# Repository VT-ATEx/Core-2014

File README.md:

Core-2014
=========

Core systems for the 2014 - 2015 school year

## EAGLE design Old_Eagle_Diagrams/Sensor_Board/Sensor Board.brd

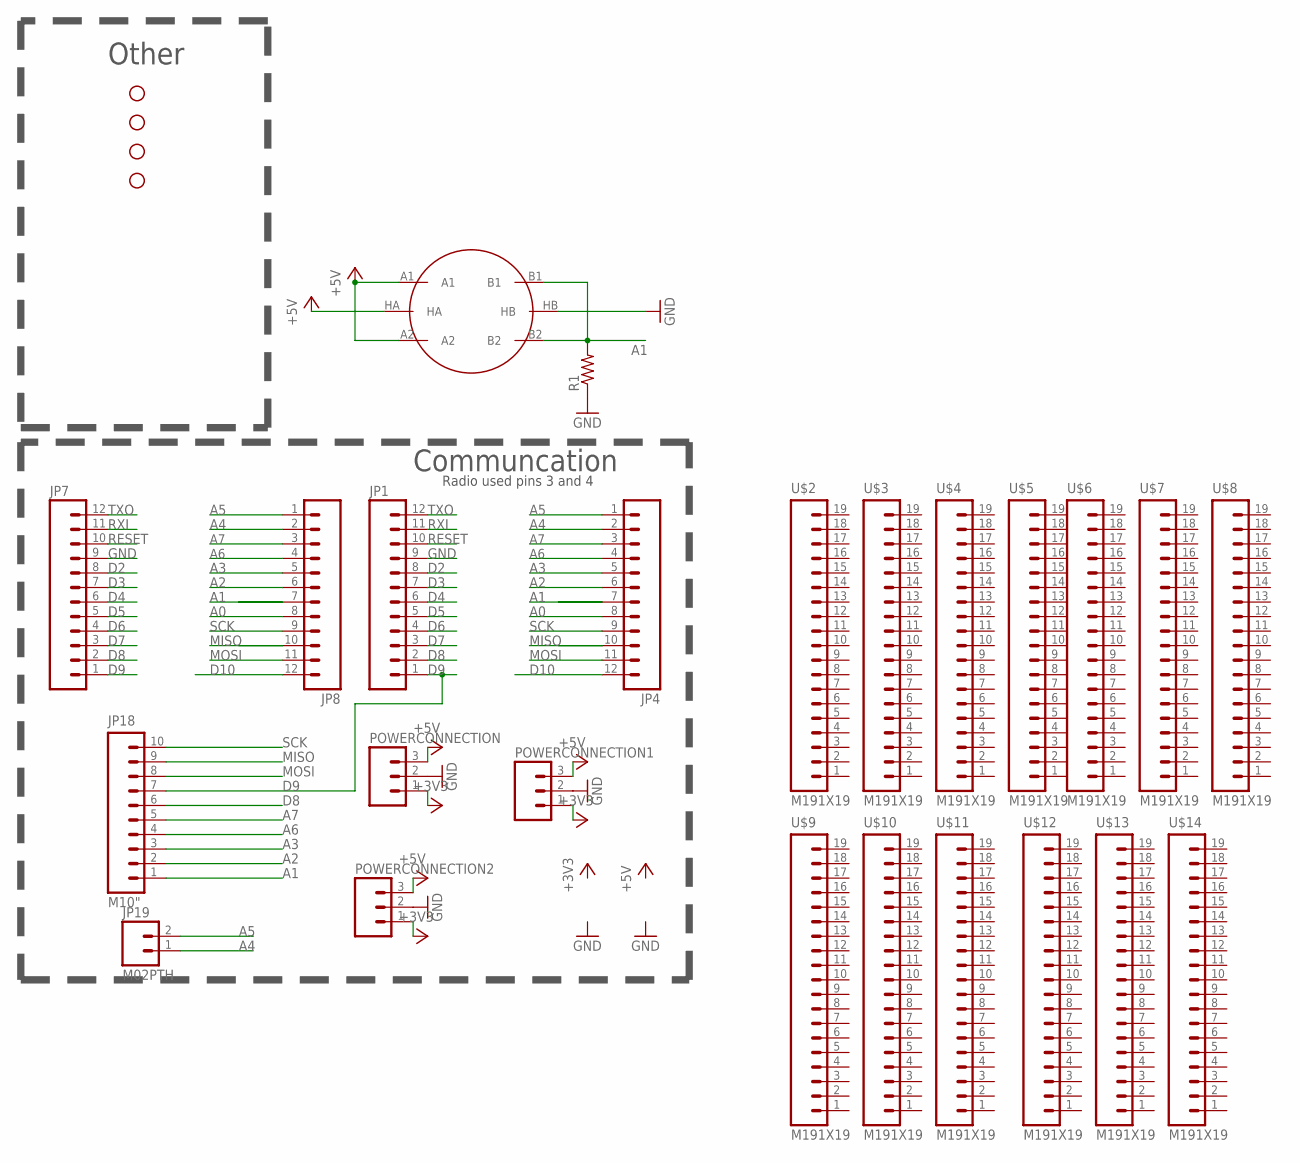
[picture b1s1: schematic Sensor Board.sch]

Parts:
JP1, JP4, JP7, JP8: M12PTH; 1X12
JP18: M10"; 1X10
JP19: M02PTH; 1X02
POWERCONNECTION, POWERCONNECTION1, POWERCONNECTION2: M03PTH; 1X03
R1: RESISTORPTH-1/4W; AXIAL-0.4
STANDOFF1, STANDOFF2, STANDOFF3, STANDOFF4: STAND-OFF
U$1: GAS_SOCKET; MQ-3
U$2, U$3, U$4, U$5, U$6, U$7, U$8, U$9, U$10, U$11, U$12, U$13, U$14: M191X19; 1X19

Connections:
+3V3: POWERCONNECTION.1, POWERCONNECTION1.1, POWERCONNECTION2.1
+5V: POWERCONNECTION.3, POWERCONNECTION1.3, POWERCONNECTION2.3, U$1.A1, U$1.A2, U$1.HA
A0: JP4.8, JP8.8
A1: JP4.7, JP8.7, JP18.1, R1.P$2 (2), U$1.B1, U$1.B2
A2: JP4.6, JP8.6, JP18.2
A3: JP4.5, JP8.5, JP18.3
A4: JP4.2, JP8.2, JP19.1
A5: JP4.1, JP8.1, JP19.2
A6: JP4.4, JP8.4, JP18.4
A7: JP4.3, JP8.3, JP18.5
D2: JP1.8, JP7.8
D3: JP1.7, JP7.7
D4: JP1.6, JP7.6
D5: JP1.5, JP7.5
D6: JP1.4, JP7.4
D7: JP1.3, JP7.3
D8: JP1.2, JP7.2, JP18.6
D9: JP1.1, JP7.1, JP18.7
D10: JP4.12, JP8.12
GND: JP1.9, JP7.9, POWERCONNECTION.2, POWERCONNECTION1.2, POWERCONNECTION2.2, R1.P$1 (1), U$1.HB
MISO: JP4.10, JP8.10, JP18.9
MOSI: JP4.11, JP8.11, JP18.8
RESET: JP1.10, JP7.10
RXI: JP1.11, JP7.11
SCK: JP4.9, JP8.9, JP18.10
TXO: JP1.12, JP7.12

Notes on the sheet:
Communcation
Other
Radio used pins 3 and 4

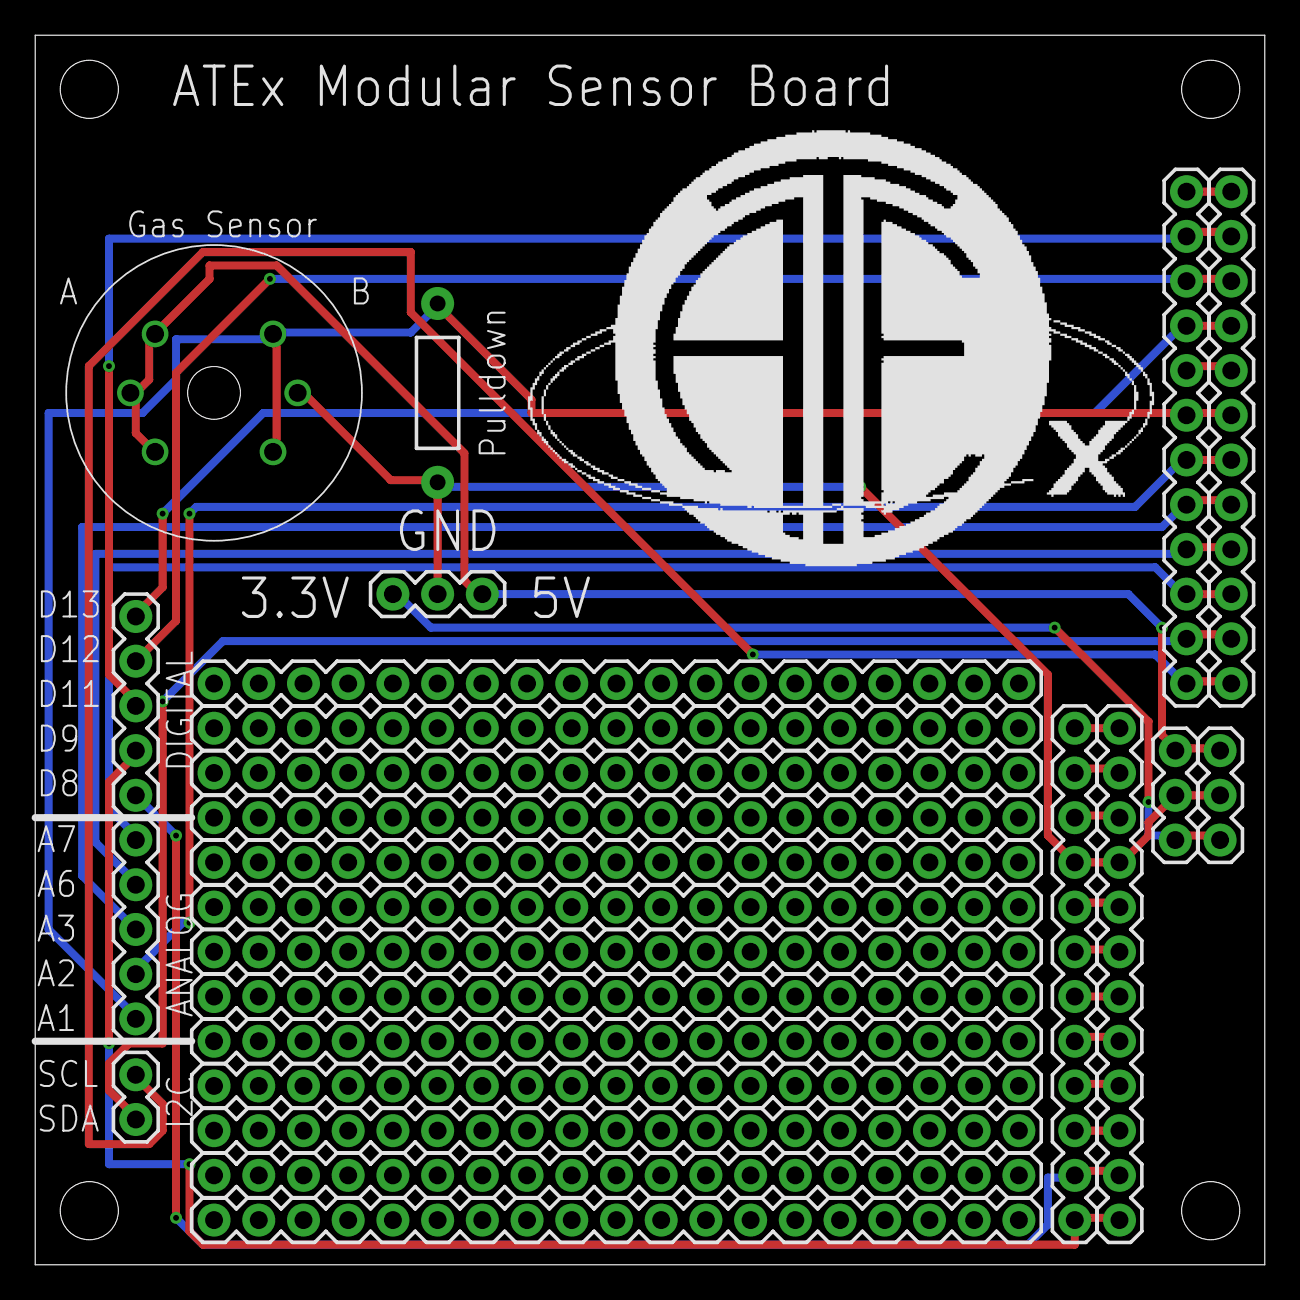
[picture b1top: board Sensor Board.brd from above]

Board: 2 copper layers, 69.8 x 69.8 mm, 28 parts (0 on the bottom side), 26 nets.

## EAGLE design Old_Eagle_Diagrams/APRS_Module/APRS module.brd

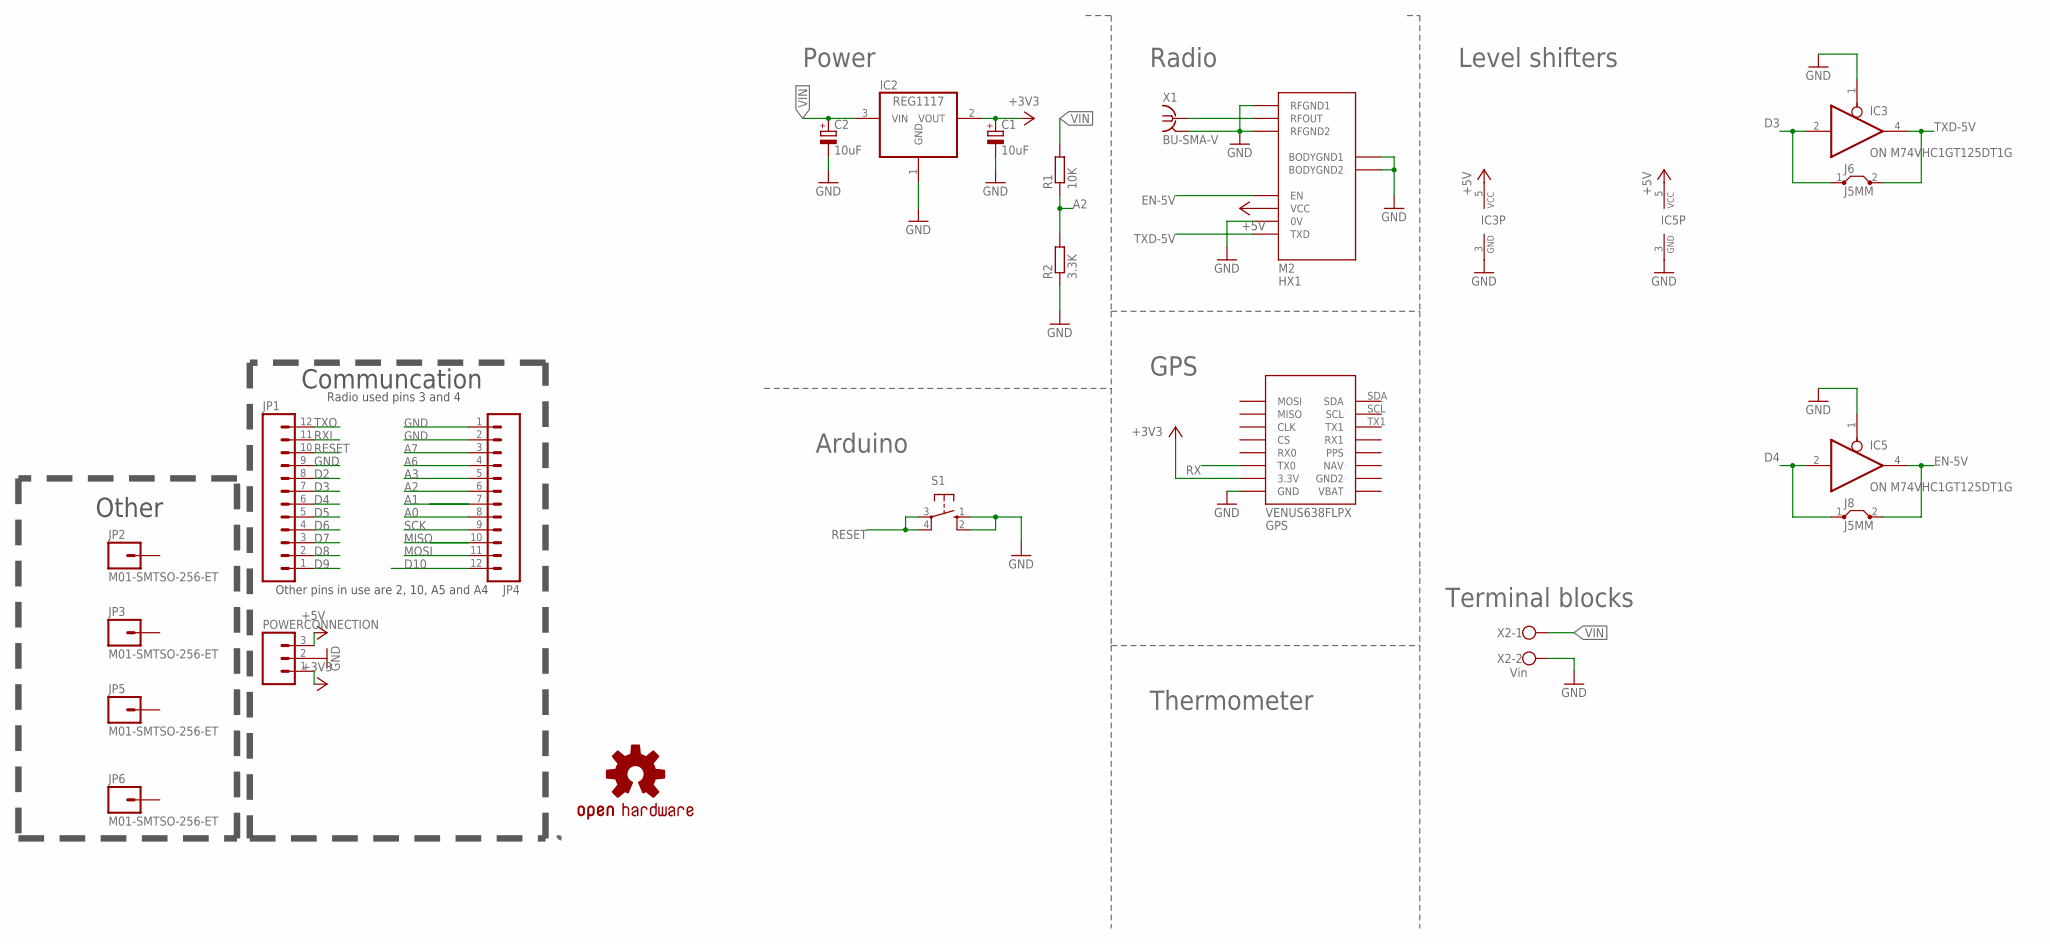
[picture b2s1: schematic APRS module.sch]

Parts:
C1, C2: 10uF; E2,5-5
GPS: VENUS638FLPX
IC2: REG1117; SOT223
IC3, IC5: ON M74VHC1GT125DT1G; SOT23-5
J6, J8: J5MM; 05
JP1, JP4: M12PTH; 1X12
JP2, JP3, JP5, JP6: M01-SMTSO-256-ET; SMTSO-256-ET
LOGO1: OSHW-LOGOL; OSHW-LOGO-L
M2: HX1
POWERCONNECTION: M03PTH; 1X03
R1: 10K; R1206
R2: 3.3K; R1206
S1: 10-XX; B3F-10XX
X1: BU-SMA-V
X2: Vin; W237-102

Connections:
+3V3: C1.+, GPS.3.3V, IC2.2 (VOUT), POWERCONNECTION.1
+5V: IC3.5 (VCC), IC5.5 (VCC), M2.VCC, POWERCONNECTION.3
A0: JP4.8
A1: JP4.7
A2: JP4.6, R1.1, R2.2
A3: JP4.5
A6: JP4.4
A7: JP4.3
D2: JP1.8
D3: IC3.2 (I), J6.1, JP1.7
D4: IC5.2 (I), J8.1, JP1.6
D5: JP1.5
D6: JP1.4
D7: JP1.3
D8: JP1.2
D9: JP1.1
D10: JP4.12
EN-5V: IC5.4 (O), J8.2, M2.EN
GND: C1.-, C2.-, GPS.GND, IC2.1 (GND), IC3.1 (OE), IC3.3 (GND), IC5.1 (OE), IC5.3 (GND), JP1.9, JP4.1, JP4.2, M2.0V, M2.BODYGND1, M2.BODYGND2, M2.RFGND1, M2.RFGND2, POWERCONNECTION.2, R2.1, S1.1 (S), S1.2 (S1), X1.2 (GND), X1.3 (GND), X1.4 (GND), X1.5 (GND), X2.2
MISO: JP4.10
MOSI: JP4.11
RESET: JP1.10, S1.3, S1.4 (P1)
RFOUT: M2.RFOUT, X1.1
RX: GPS.TX0
RXI: JP1.11
SCK: JP4.9
TXD-5V: IC3.4 (O), J6.2, M2.TXD
TXO: JP1.12
VIN: C2.+, IC2.3 (VIN), R1.2, X2.1

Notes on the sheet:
Communcation
Other
Radio used pins 3 and 4
Other pins in use are 2, 10, A5 and A4
Level shifters
Power
Arduino
Radio
GPS
Thermometer
Terminal blocks

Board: 2 copper layers, 22 parts (0 on the bottom side), 11 nets, no tracks yet.

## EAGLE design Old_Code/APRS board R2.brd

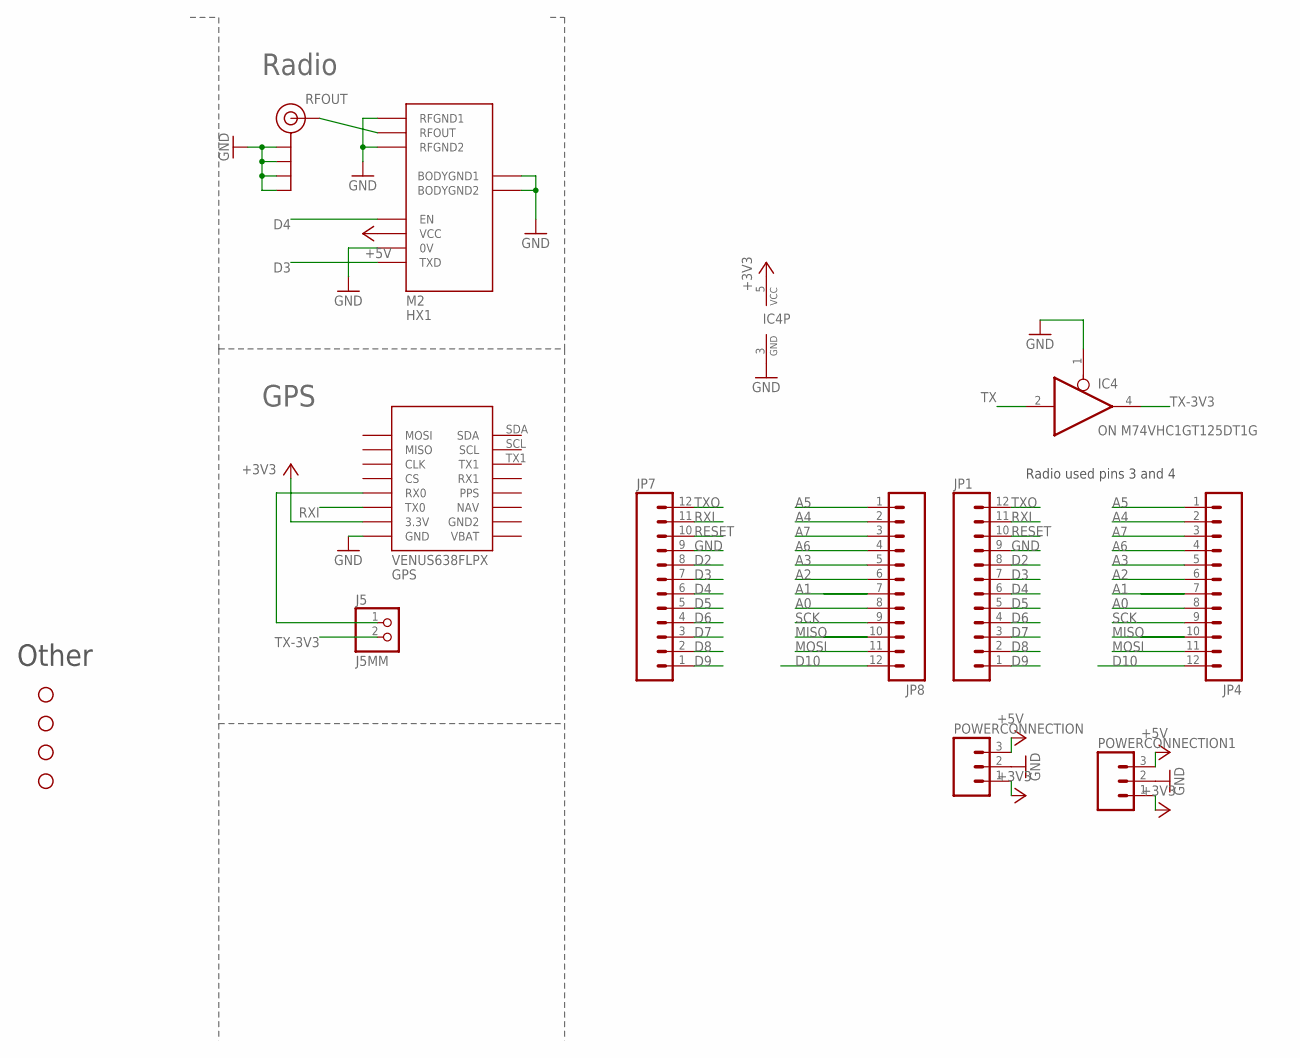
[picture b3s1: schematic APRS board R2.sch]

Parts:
GPS: VENUS638FLPX
IC4: ON M74VHC1GT125DT1G; SOT23-5
J5: J5MM; 1X02
J$1: SMA_EDGE; SMA-EDGE
JP1, JP4, JP7, JP8: M12PTH; 1X12
M2: HX1
POWERCONNECTION, POWERCONNECTION1: M03PTH; 1X03
STANDOFF1, STANDOFF2, STANDOFF3, STANDOFF4: STAND-OFF

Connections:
+3V3: GPS.3.3V, IC4.5 (VCC), POWERCONNECTION.1, POWERCONNECTION1.1
+5V: M2.VCC, POWERCONNECTION.3, POWERCONNECTION1.3
A0: JP4.8, JP8.8
A1: JP4.7, JP8.7
A2: JP4.6, JP8.6
A3: JP4.5, JP8.5
A4: JP4.2, JP8.2
A5: JP4.1, JP8.1
A6: JP4.4, JP8.4
A7: JP4.3, JP8.3
D2: JP1.8, JP7.8
D3: JP1.7, JP7.7, M2.TXD
D4: JP1.6, JP7.6, M2.EN
D5: JP1.5, JP7.5
D6: JP1.4, JP7.4
D7: JP1.3, JP7.3
D8: JP1.2, JP7.2
D9: JP1.1, JP7.1
D10: JP4.12, JP8.12
GND: GPS.GND, IC4.1 (OE), IC4.3 (GND), J$1.GND@0 (GND), J$1.GND@1 (GND), J$1.GND@2 (GND), J$1.GND@3 (GND), JP1.9, JP7.9, M2.0V, M2.BODYGND1, M2.BODYGND2, M2.RFGND1, M2.RFGND2, POWERCONNECTION.2, POWERCONNECTION1.2
MISO: JP4.10, JP8.10
MOSI: JP4.11, JP8.11
unnamed: GPS.RX0, J5.1
RESET: JP1.10, JP7.10
RFOUT: J$1.SIG (SIGNAL), M2.RFOUT
RXI: GPS.TX0, JP1.11, JP7.11
SCK: JP4.9, JP8.9
TX: IC4.2 (I)
TX-3V3: IC4.4 (O), J5.2
TXO: JP1.12, JP7.12

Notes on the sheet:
Other
Radio used pins 3 and 4
Radio
GPS

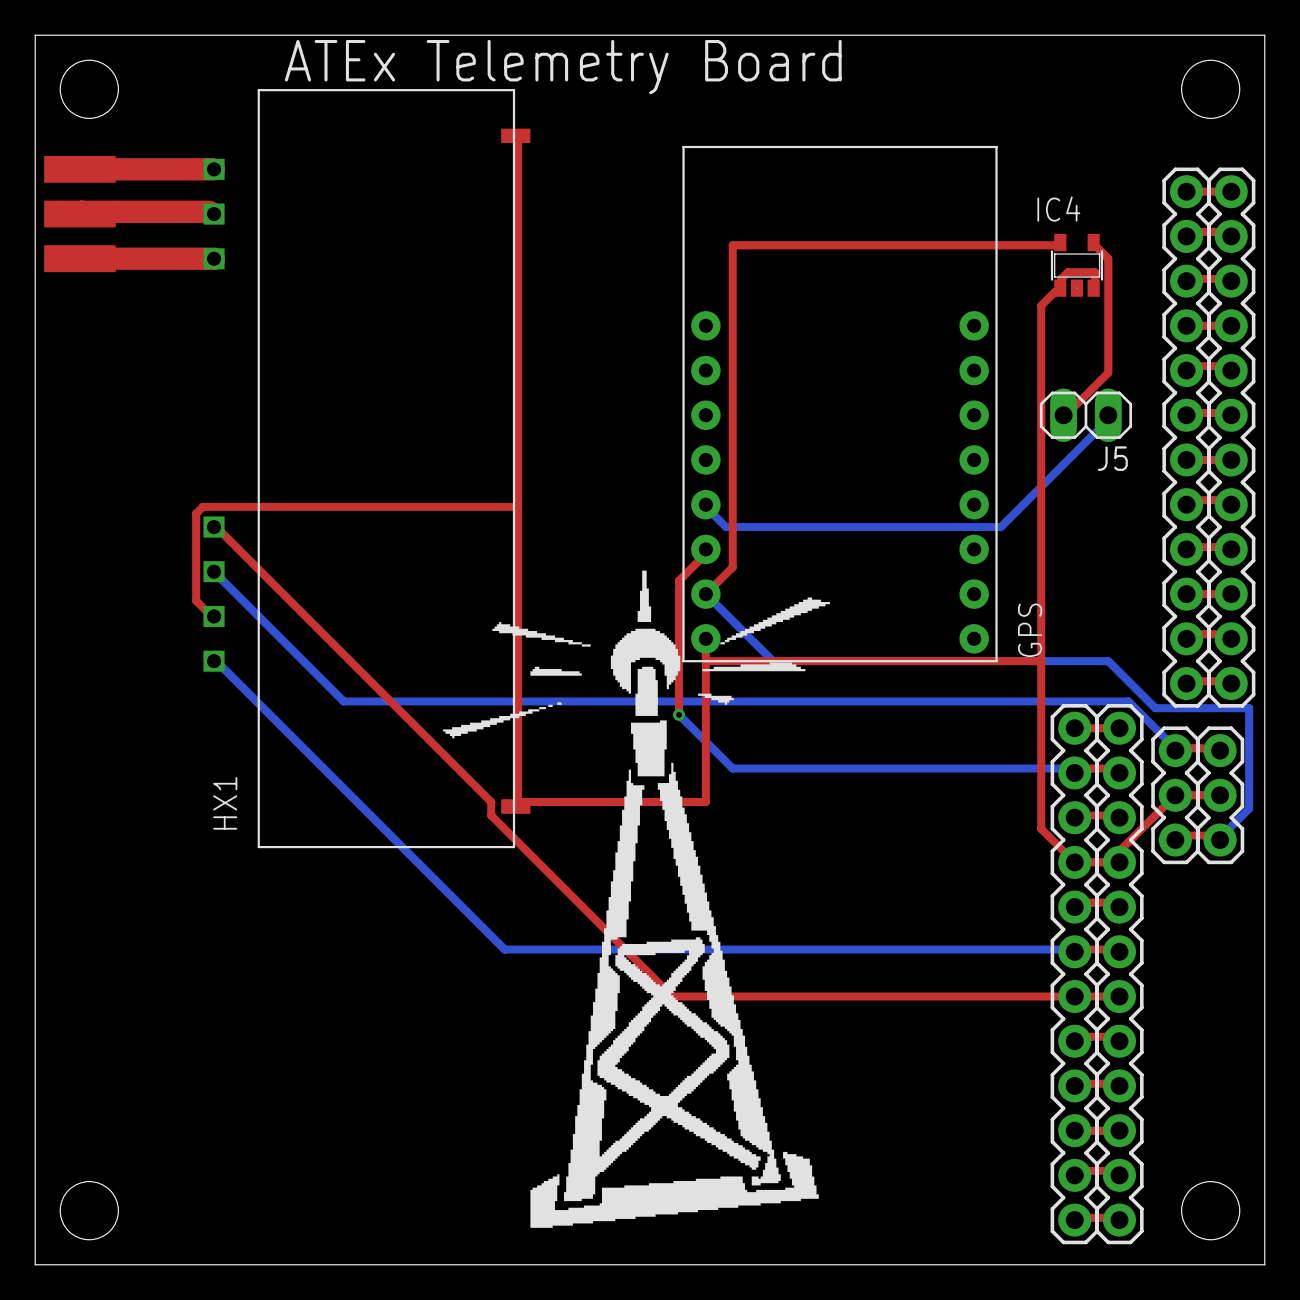
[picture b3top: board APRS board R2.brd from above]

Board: 2 copper layers, 69.8 x 69.8 mm, 15 parts (0 on the bottom side), 29 nets.

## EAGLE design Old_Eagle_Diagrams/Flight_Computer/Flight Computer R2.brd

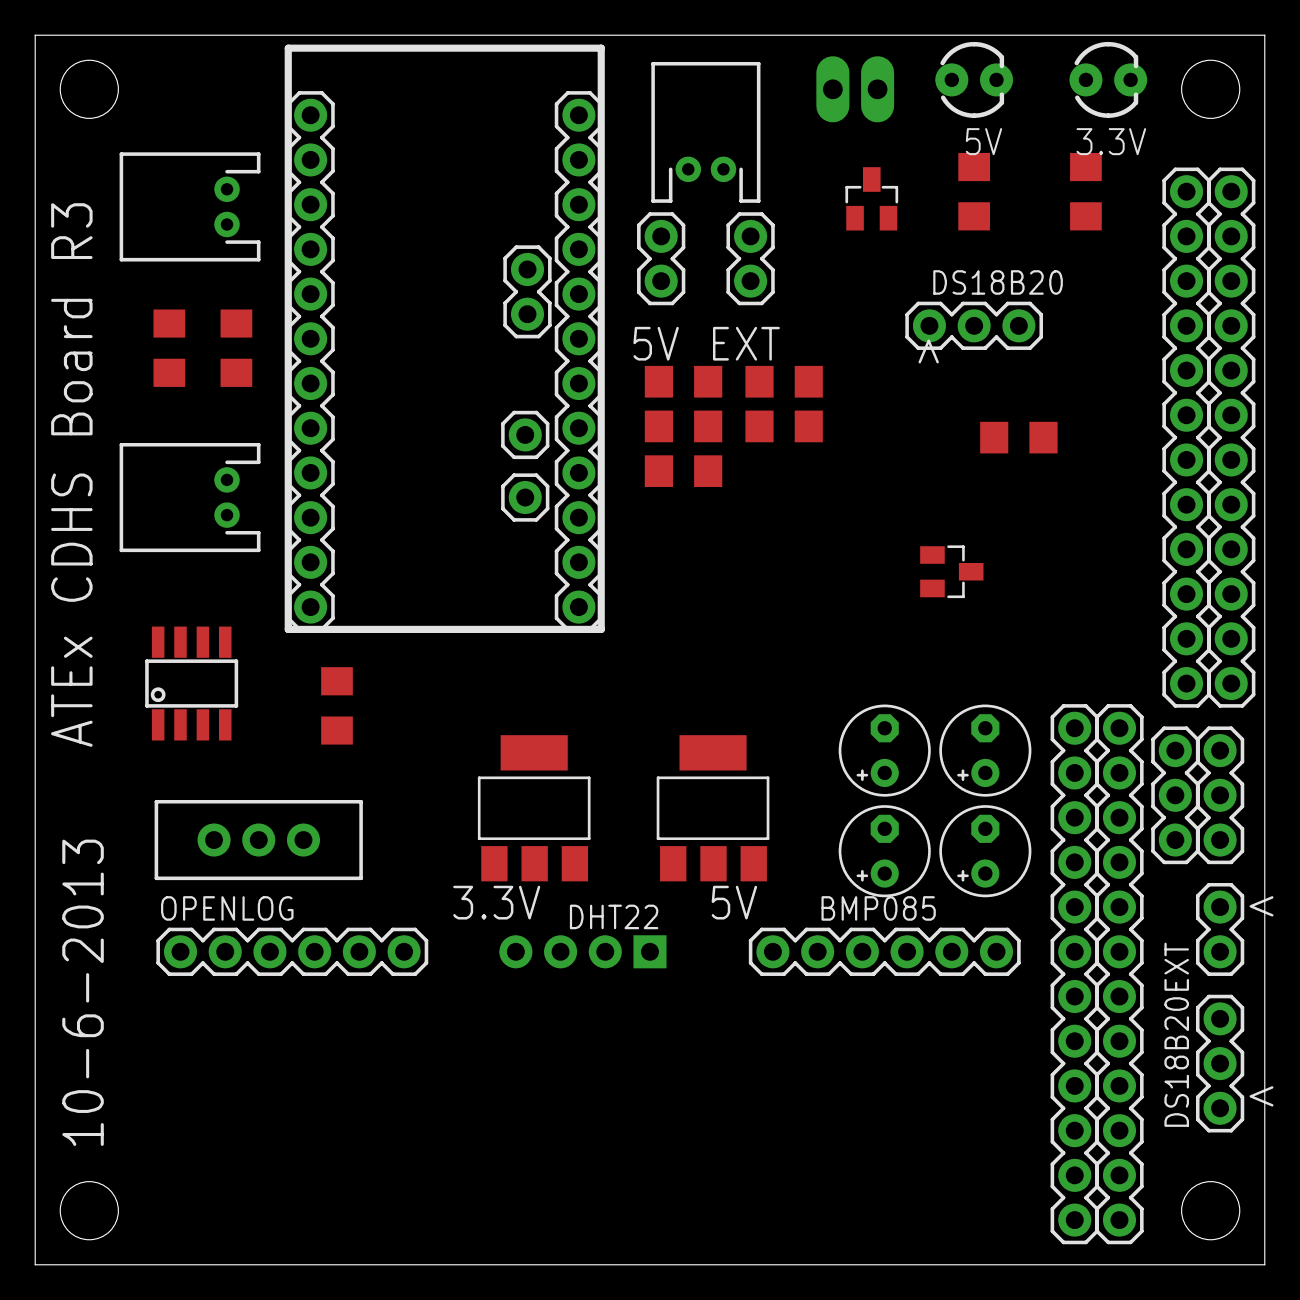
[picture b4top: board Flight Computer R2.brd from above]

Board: 2 copper layers, 69.8 x 69.8 mm, 50 parts (0 on the bottom side), 37 nets, no tracks yet.

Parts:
BMP085: 1X06
C1, C6: .1 uF; 1206
C2, C3, C4, C5: 10uF; E2,5-5
DHT22: 1X04_NO_SILK
DS18B20, DS18B20EXT: 1X03
HEATERELEMENT: M02PTH3; 1X02_LONGPADS
IC1, IC2: REG1117; SOT223
JP1, JP4, JP7, JP8, JP12, JP13: 1X12
JP3, JP5, JP6: M02JST-PTH-2; JST-2-PTH
JP9, JP10: M02PTH; 1X02
JP11, JP15: 1X02
JP17, JP18: 1X01
LED1, LED2: LED3MM
OPENLOG: 1X06
POWERCONNECTION, POWERCONNECTION1: 1X03
Q3, Q4: SST5484; SOT23
R1, R7, R8, R10: 10K; 1206
R2, R3, R33: 4.7k; 1206
R5: 5K; 1206
R11: 2.5k; 1206
S1: SWITCH-SPDT
STANDOFF1, STANDOFF2, STANDOFF3, STANDOFF4: STAND-OFF
U$1: IRF9389TRPBF; SO-8

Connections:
3.7V: HEATERELEMENT.2, JP9.2, JP10.2
3VOLT: LED1.A, R2.1
5VOLT: LED2.A, R3.1
+3V3: C2.+, C6.2, IC2.2, POWERCONNECTION.1, POWERCONNECTION1.1, R2.2
+5V: BMP085.1, C1.2, C4.+, DHT22.1, DS18B20.1, DS18B20EXT.1, IC1.2, JP10.1, JP11.2, JP13.4, OPENLOG.4, POWERCONNECTION.3, POWERCONNECTION1.3, R1.2, R3.2, R33.2
A0: JP4.8, JP8.8, JP13.8, R10.1, R11.2
A1: JP4.7, JP8.7, JP13.7
A2: JP4.6, JP8.6, JP13.6
A3: JP4.5, JP8.5, JP13.5
A4: BMP085.3, JP4.2, JP8.2, JP15.1
A5: BMP085.2, JP4.1, JP8.1, JP15.2
A6: JP4.4, JP8.4, JP18.1
A7: JP4.3, JP8.3, JP17.1
D2: DS18B20.2, DS18B20EXT.2, JP1.8, JP7.8, JP12.8, R33.1
D3: JP1.7, JP7.7, JP12.7
D4: JP1.6, JP7.6, JP12.6
D5: DHT22.2, JP1.5, JP7.5, JP12.5, R1.1
D6: JP1.4, JP7.4, JP12.4, Q3.1, R8.2
D7: JP1.3, JP7.3, JP12.3, U$1.2
D8: JP1.2, JP7.2, JP12.2
D9: JP1.1, JP7.1, JP12.1
D10: JP4.12, JP8.12, JP13.12, Q4.1, R7.2
GND: BMP085.6, C1.1, C2.-, C3.-, C4.-, C5.-, C6.1, DHT22.4, DS18B20.3, DS18B20EXT.3, IC1.1, IC2.1, JP1.9, JP3.1, JP5.1, JP7.9, JP12.9, JP13.2, LED1.K, LED2.K, OPENLOG.5, OPENLOG.6, POWERCONNECTION.2, POWERCONNECTION1.2, Q3.2, Q4.2, R7.1, R8.1, R11.1, U$1.1
LEDCONTROL: JP11.1, Q3.3
MISO: JP4.10, JP8.10, JP13.10
MOSI: JP4.11, JP8.11, JP13.11
unnamed: HEATERELEMENT.1, Q4.3
unnamed: OPENLOG.2, S1.2
unnamed: JP6.2, R5.2, U$1.3
unnamed: JP5.2, JP6.1
unnamed: R5.1, U$1.4, U$1.7
unnamed: JP3.2, JP9.1
RAW: C3.+, C5.+, IC1.3, IC2.3, JP13.1, R10.2, U$1.5
RESET: JP1.10, JP7.10, JP12.10, JP13.3
RXI: JP1.11, JP7.11, JP12.11
SCK: JP4.9, JP8.9, JP13.9
TXO: JP1.12, JP7.12, JP12.12, S1.1

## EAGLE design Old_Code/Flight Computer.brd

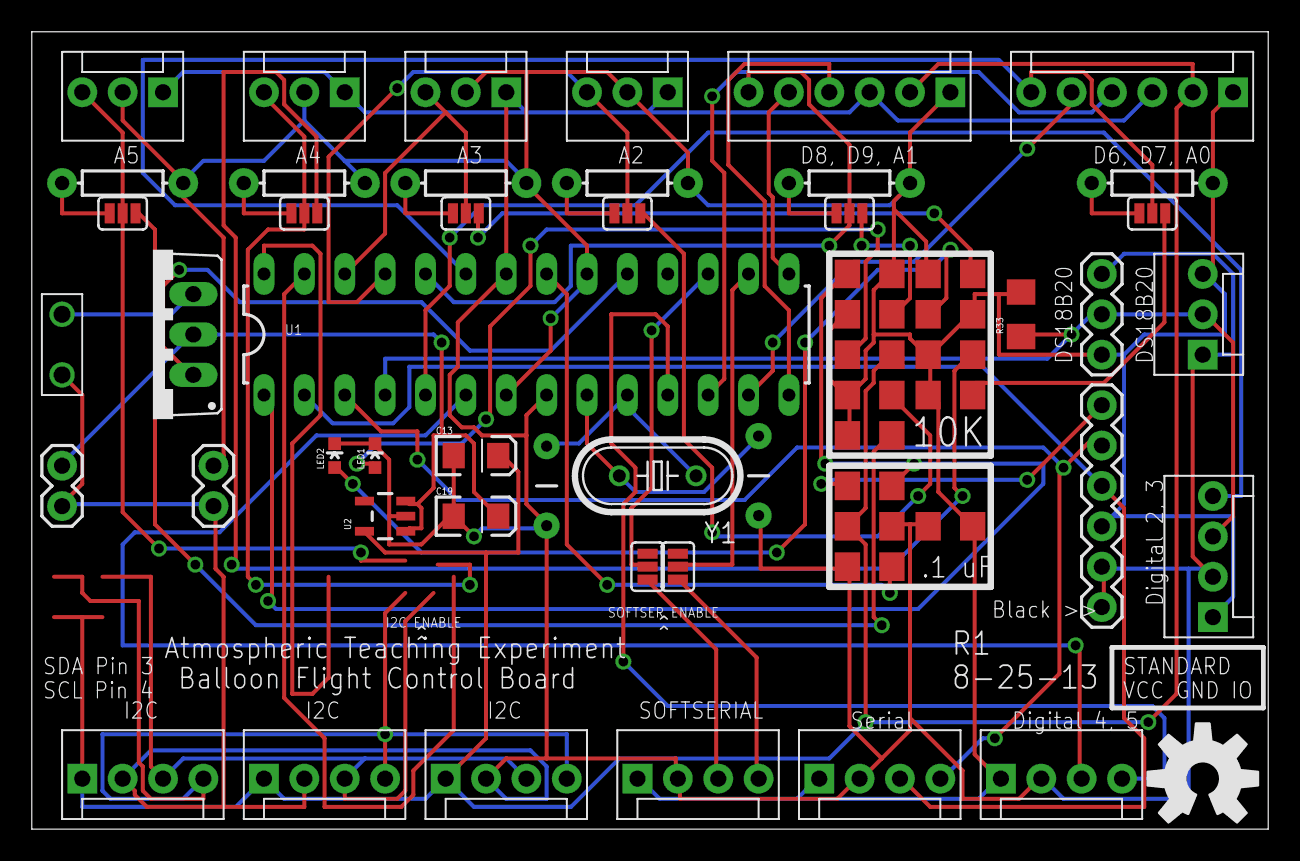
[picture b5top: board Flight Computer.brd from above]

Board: 2 copper layers, 77.8 x 50.2 mm, 58 parts (0 on the bottom side), 47 nets.

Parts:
A0R, A1R, A2R, A3R, A4R, A5R: AXIAL-0.3
A0S, A1S, A2S, A3S, A4S, A5S: SJ_3_PASTE2&3
A2, A3, A4, A5: MOLEX-1X3
C1, C3, C4: .1 uF; 1206
C5, C6: 22 pF; CAP-PTH-5MM
C11: 0.1uF; 1206
C13, C19: 10uF; EIA3216
DIGITAL2,3, DIGITAL4,5: MOLEX-1X4
DS18B20: 1X03
DS18B20EXT: MOLEX-1X3
I2C1, I2C2, I2C3: MOLEX-1X4
JP1: FTDI Basic; 1X06
JP2, JP3: M02PTH; 1X02
JP4: M02PTH2; 1X02_BIG
LED1: Red; LED-0603
LED2: Green; LED-0603
LOGO1: OSHW-LOGOL; OSHW-LOGO-L
MULTI1, MULTI2: MOLEX-1X6
Q1: TO220BV
R1: 10k; 1206
R4, R5, R9, R11, R12, R14, R17, R18: 10K; 1206
R33: 4.7k; 1206
SERIAL: MOLEX-1X4
SOFTSERIAL: MOLEX-1X4
SOFTSERIALR: SJ_3_PASTE2&3
SOFTSERIALT: SJ_3_PASTE2&3
U1: ATMEGA328P_PDIP; DIL28-3
U2: MIC5205; SOT23-5
Y1: HC49U-V

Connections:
+3V3: C11.1, C13.A, I2C1.1, I2C2.1, I2C3.1, MULTI1.2, MULTI2.2, R11.2, U2.5
+5V: A0R.P$2, A1R.P$2, A2.2, A2R.P$2, A3.2, A3R.P$2, A4.2, A4R.P$2, A5.2, A5R.P$2, C1.2, DIGITAL2,3.1, DIGITAL4,5.1, DS18B20.3, DS18B20EXT.3, JP1.4, JP3.2, MULTI1.1, MULTI2.1, R1.2, R4.2, R5.1, R9.1, R12.1, R14.1, R17.1, R18.1, R33.2, SERIAL.1, SOFTSERIAL.1, U1.7, U1.20
A0: A0S.2, MULTI1.6, U1.23
A1: A1S.2, MULTI2.6, U1.24
A2: A2.3, A2S.2, U1.25
A3: A3.3, A3S.2, U1.26
A4: A4.3, A4S.2
A5: A5.3, A5S.2
D2: DIGITAL2,3.3, DS18B20.2, DS18B20EXT.2, R33.1, U1.4
D3: DIGITAL2,3.4, U1.5
D4: DIGITAL4,5.3, U1.6
D5: DIGITAL4,5.4, U1.11
D6: MULTI1.4, U1.12
D7: MULTI1.5, U1.13
D8: MULTI2.4, U1.14
D9: MULTI2.5, U1.15
D13: Q1.G, U1.19
DTR: C3.1, JP1.1
GND: A2.1, A3.1, A4.1, A5.1, C1.1, C4.1, C5.1, C6.1, C11.2, C13.C, C19.C, DIGITAL2,3.2, DIGITAL4,5.2, DS18B20.1, DS18B20EXT.1, I2C1.2, I2C2.2, I2C3.2, JP1.5, JP1.6, JP2.1, JP3.1, JP4.P$1, LED1.C, LED2.C, MULTI1.3, MULTI2.3, SERIAL.2, SOFTSERIAL.2, U1.8, U1.22, U2.2
unnamed: C5.2, U1.9, Y1.2
unnamed: C6.2, U1.10, Y1.1
unnamed: LED2.A, R4.1
unnamed: A0S.3, R5.2
unnamed: C4.2, U1.21
unnamed: JP4.P$2, Q1.S
unnamed: C3.2, R1.1, U1.1
unnamed: A1S.3, R9.2
unnamed: A2S.3, R12.2
unnamed: A3S.3, R14.2
unnamed: A4S.3, R17.2
unnamed: A5S.3, R18.2
unnamed: A5R.P$1, A5S.1
unnamed: A4R.P$1, A4S.1
unnamed: A3R.P$1, A3S.1
unnamed: A2R.P$1, A2S.1
unnamed: A1R.P$1, A1S.1
unnamed: A0R.P$1, A0S.1
unnamed: LED1.A, R11.1
PB2: SOFTSERIALT.2, U1.16
PB3: SOFTSERIALR.2, U1.17
RXI: JP1.3, SERIAL.3, U1.2
SCL: I2C1.4, I2C2.4, I2C3.4
SDA: I2C1.3, I2C2.3, I2C3.3
SOFTRXI: SOFTSERIAL.3, SOFTSERIALR.1
SOFTTXO: SOFTSERIAL.4, SOFTSERIALT.1
TXO: JP1.2, SERIAL.4, U1.3
VDD: C19.A, JP2.2, Q1.D, U2.1, U2.3

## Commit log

2014-09-07 Added libraries and other pre-existing code
2014-09-07 Revert "Added libraries and other pre-existing code"
    This reverts commit ec3cd4958fc64a83fee64d5323ee31a3a7482ef3.
2014-09-07 Added C, C++ libraries for sensors, etc
2014-09-07 Revert "Initial commit"
    This reverts commit 11f72e45b686f7d2dfb3feb96417e4875b00074b.
2014-09-07 Revert "Added C, C++ libraries for sensors, etc"
    This reverts commit dce734240ee0c8c5eaa0796e9b9c9aecf42fbe02.
2014-09-07 Revert "Revert "Added C, C++ libraries for sensors, etc""
    This reverts commit 16606da0ceaf8cfbd3c57e8c027e1a296371fe93.
2014-09-18 Finally solved my github problem! Added in all of the old code William put on the GDrive. -Peter
2014-09-21 Names shift in chaos Sacrificed for logic Organization
2014-10-24 Code added to Git / Everything in a single place / Where is everyone?
2014-10-24 Forgot PiFm / I have been up for too long / Sleep is for the weak
2014-11-02 just added philip.txt, which makes everything soo much gooler
2014-11-09 Raspberry Pi Files
    Code that is currently on the Pi for the SSTV stuff. The sstvcam.sh
    file is the one that currently transmits the images taken, the other .sh
    in the pisstv folder is primarily for testing. The pifm.c code is in
    the pisstv folder as well. I changed the frequency and some clock
    properties in that.
2014-12-10 My commit message
2015-02-06 Example sensor is up. E-mail me with questions.
2015-02-06 Moved some files around.
2015-02-06 Changed magnetometer code over to new sensor.
2015-02-06 Wrote cpp version of sensor code and fixed misc. errors
2015-02-08 Uploaded angular displacement calulator for ITG
2015-02-08 The uploaded BMP program needs its includes!
2015-02-08 Uploaded program for ITG3200 which reads in Regsiter values and displays them
2015-02-15 Test code was written, Phillip's code was added, changes were meade to HMC code
2015-02-20 Added code for LIS331 and added comments to sensor control code
2015-02-20 Added callsign to Trackduino code
2015-02-20 Update and rename Test to Test/test_github
2015-02-22 Uploaded new ITG3200 and BMP 180 code which are now both in the form of classes
2015-02-27 Fixed bug in LIS331
2015-02-27 Moved new LIS331 code to more sane place
2015-02-27 Fixed hex error in LIS331
2015-02-28 Added the latest BMP180 and ITG3200 programs. Includes example.
2015-03-01 Fixed HMC code
2015-03-01 Ficed bus addressing in PeterTest
2015-03-01 FIxed another HMC bug
2015-03-01 ANother bug
2015-03-01 Changed PeterTest
2015-03-01 Fixed HMCTest
2015-03-01 Maybe?
2015-03-17 Added self-test function to HMC and potentially fixed errors
2015-03-22 Added cutdown function
2015-03-26 Delete CAPE-ESA-01-00A0.dtbo
    Adds nothing to current code development.
2015-03-26 Delete CAPE-ESA-01-00A0.dts
    Adds nothing to current code development
2015-03-26 Delete CAPE-POWER-01-00A0.dtbo
    Adds nothing to current code development and is outdated
2015-03-26 Delete CAPE-POWER-01-00A0.dts
    Adds nothing to current code development and is outdated
2015-03-26 Create Example.dts
    Added up-date example of a .dts file.
2015-03-26 Delete GPIO.cpp.svn-base
    Not need as we are not using svn, cleaning files up a bit
2015-03-26 Delete GPIO.h.svn-base
    Not need as we are not using svn, cleaning files up a bit
2015-03-26 Delete SimpleGPIO.cpp.svn-base
    Not need as we are not using svn, cleaning files up a bit
2015-03-26 Delete SimpleGPIO.h.svn-base
    Not need as we are not using svn, cleaning files up a bit
2015-03-26 Delete TempChamberTesting.cpp.svn-base
    Not need as we are not using svn, cleaning files up a bit
2015-03-26 Delete all-wcprops
    Not need as we are not using svn, cleaning files up a bit
2015-03-26 Delete entries
    Not need as we are not using svn, cleaning files up a bit
2015-03-26 Delete ADC.cpp.svn-base
    Not need as we are not using svn, cleaning files up a bit
2015-03-26 Delete ADC.h.svn-base
    Not need as we are not using svn, cleaning files up a bit
2015-03-26 Delete ChipCap2.cpp.svn-base
    Not need as we are not using svn, cleaning files up a bit
2015-03-26 Delete ChipCap2.h.svn-base
    Not need as we are not using svn, cleaning files up a bit
2015-03-26 Delete I2C.cpp.svn-base
    Not need as we are not using svn, cleaning files up a bit
2015-03-26 Delete I2C.h.svn-base
    Not need as we are not using svn, cleaning files up a bit
2015-03-26 Delete LIS331.cpp.svn-base
    Not need as we are not using svn, cleaning files up a bit
2015-03-26 Delete LIS331.h.svn-base
    Not need as we are not using svn, cleaning files up a bit
2015-03-26 Delete LM73.cpp.svn-base
    Not need as we are not using svn, cleaning files up a bit
2015-03-26 Delete LM73.h.svn-base
    Not need as we are not using svn, cleaning files up a bit
2015-03-26 Delete RTC.cpp.svn-base
    Not need as we are not using svn, cleaning files up a bit
2015-03-26 Delete RTC.h.svn-base
    Not need as we are not using svn, cleaning files up a bit
2015-03-26 Delete SPI.cpp.svn-base
    Not need as we are not using svn, cleaning files up a bit
2015-03-26 Delete SPI.h.svn-base
    Not need as we are not using svn, cleaning files up a bit
2015-03-26 Delete UART.cpp.svn-base
    Not need as we are not using svn, cleaning files up a bit
2015-03-26 Delete UART.h.svn-base
    Not need as we are not using svn, cleaning files up a bit
2015-03-26 Delete serialib.cpp.svn-base
    Not need as we are not using svn, cleaning files up a bit
2015-03-26 Delete serialib.h.svn-base
    Not need as we are not using svn, cleaning files up a bit
2015-03-26 Delete adctest.cpp.svn-base
    Not need as we are not using svn, cleaning files up a bit
2015-03-26 Delete GPIOTEST.cpp.svn-base
    Not need as we are not using svn, cleaning files up a bit
2015-03-26 Delete Test.svn-base
    Not need as we are not using svn, cleaning files up a bit
2015-03-26 Delete ChipCap2Test.cpp.svn-base
    Not need as we are not using svn, cleaning files up a bit
2015-03-26 Delete I2CTest.cpp.svn-base
    Not need as we are not using svn, cleaning files up a bit
2015-03-26 Delete LM73Test.cpp.svn-base
    Not need as we are not using svn, cleaning files up a bit
2015-03-26 Delete RTCtest.cpp.svn-base
    Not need as we are not using svn, cleaning files up a bit
2015-03-26 Delete UARTTest.cpp.svn-base
    Not need as we are not using svn, cleaning files up a bit
2015-03-26 Delete uartecho.cpp.svn-base
    Not need as we are not using svn, cleaning files up a bit
2015-03-26 Delete adc.c.svn-base
    Not need as we are not using svn, cleaning files up a bit
2015-03-26 Delete gpio.c.svn-base
    Not need as we are not using svn, cleaning files up a bit
2015-03-26 Delete chipCap2.c.svn-base
    Not need as we are not using svn, cleaning files up a bit
2015-03-26 Delete i2c.c.svn-base
    Not need as we are not using svn, cleaning files up a bit
2015-03-26 Delete lm73.c.svn-base
    Not need as we are not using svn, cleaning files up a bit
2015-03-26 Delete uart.c.svn-base
    Not need as we are not using svn, cleaning files up a bit
2015-03-26 Delete adctest.svn-base
    Not need as we are not using svn, cleaning files up a bit
2015-03-26 Delete adctest.c.svn-base
    Not need as we are not using svn, cleaning files up a bit
2015-03-26 Delete ledmodulus.c.svn-base
    Not need as we are not using svn, cleaning files up a bit
2015-03-26 Delete i2clibtest.c.svn-base
    Not need as we are not using svn, cleaning files up a bit
2015-03-26 Delete uarttest.c.svn-base
    Not need as we are not using svn, cleaning files up a bit
2015-03-27 Complete code library is in test/INTEGRATED_TEST, please read the README file before editing anything.
2015-03-27 Fixed cutdown mechanism
2015-04-05 Improved the LM73 temperature test code such that it compiles and runs.
2015-04-05 Added folder "Individual_Sensors_Tests", which has seperate folders that test each sensor seperately. Folder added to /Libraries/cppfiles/tests
2015-04-05 Made small modification to LM73Test.cpp
2015-04-09 Added ALL_Test_phil1, a full single thread test of all the sensors. They all seem to work except the HMC, where the HMC individual program works, but the HMC by itself in the program doesn't. Some of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
2015-04-12 Added LED to cutdown, fixed PeterTest
2015-04-12 Added cutdown test
2015-04-16 Still a work in progress. A program that will soon be able to be used as a backup
2015-04-16 Made changeds to backup main. still needs some stuff
2015-04-16 Fixed cutdown issue in PeterTest
2015-04-16 Added sanity check to cutdown
2015-04-16 Fixed HMC size error
2015-04-19 Fixed file error maybe
2015-04-23 Uploaded some main that takes data

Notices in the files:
parts and their libraries:
SparkFun-Connectors: Licensing: CC v3.0 Share-Alike You are welcome to use this library for commercial purposes.
